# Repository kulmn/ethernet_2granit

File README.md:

# Устройство прозрачной передачи данных с КП «Гранит» («Гранит М») через Ethernet сеть.

Непосредственно опрашивает КП, ответ упаковывает в UDP пакет и отправляет на указанный IP и порт. Приёмная сторона передаёт данные в последовательный порт.

- веб интерфейс настройки параметров (IP адрес, шлюз, скорость портов, адреса КП) 
- 1 Ethernet и 2 последовательных порта
- кнопка сброса к заводским настройкам
- Сторожевой таймер

Hardware:
- Schematic diagram (Autodesk EAGLE and PDF) in /schematic/ dir
- MCU: STM32F030K6
- ENC28J60 china module

Firmvare:
- GCC Eclipse project, FreeRTOS, LibopenCM3

##### !!! Использовать только в защищённых сетях !!!

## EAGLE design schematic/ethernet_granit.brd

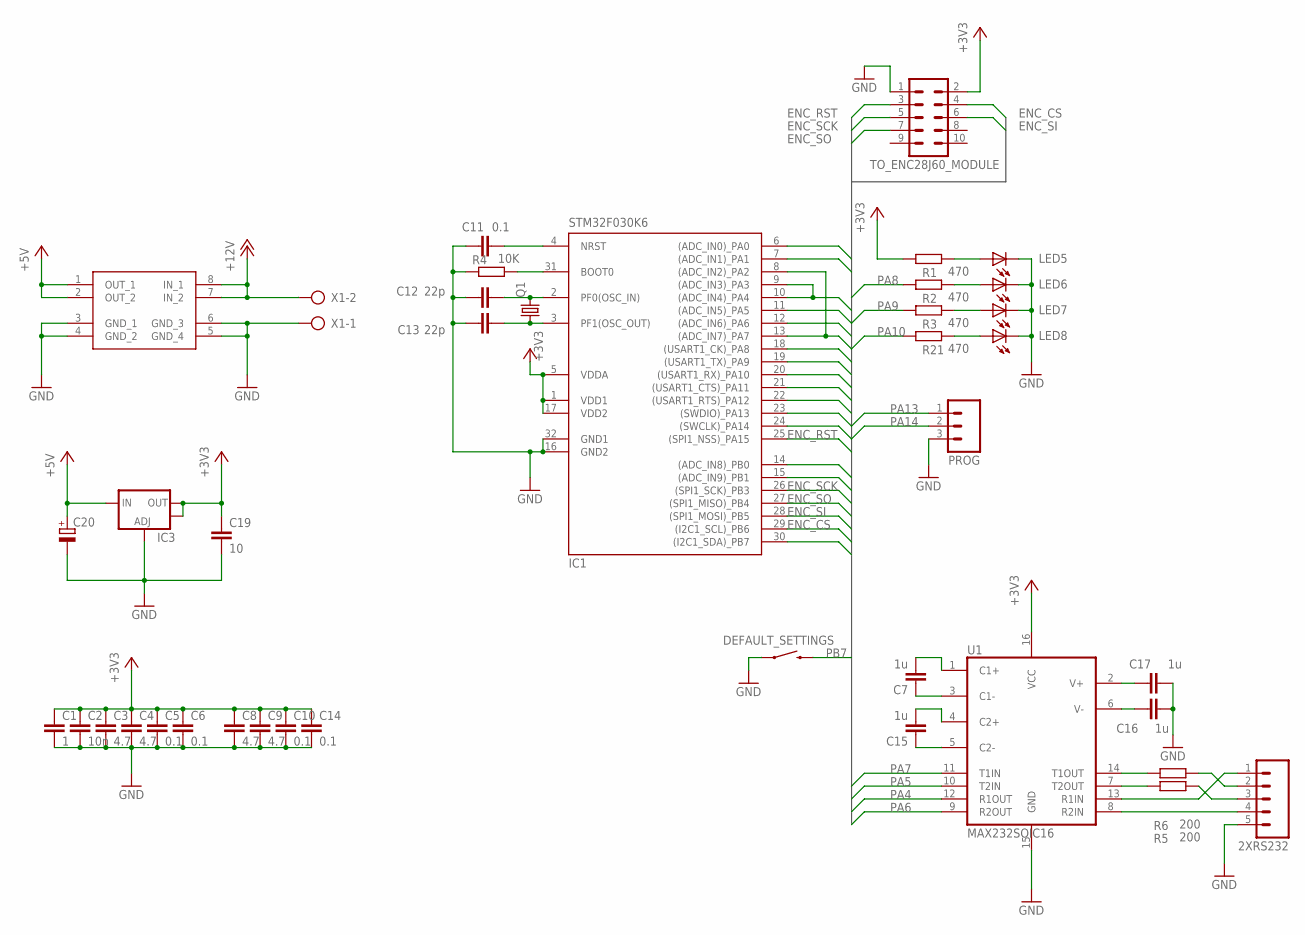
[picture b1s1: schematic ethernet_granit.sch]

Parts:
2XRS232: M05; 05P
C1: 1; C0805
C2: 10n; C0805
C3, C4, C8, C9: 4.7; C0805
C5, C6, C10, C11, C14: 0.1; C0805
C7, C15, C16, C17: 1u; C0805
C12, C13: 22p; C0805
C19: 10; C0805
C20: CPOL-EUSMCC; SMC_C
DEFAULT_SETTINGS: SWITCH-MOMENTARY-2SIDE_EZ; TACTILE-PTH-SIDEEZ
IC1: STM32F030K6; TQFP32-08
IC3: V_REG_LM1117SOT223; SOT223
LED5, LED6, LED7, LED8: TLLG4400; LED3MM
PROG: M03; 03P
Q1: CRYSTALHC49S; HC49/S
R1, R2, R3, R21: 470; R0805
R4: 10K; R0805
R5, R6: 200; R0805
TO_ENC28J60_MODULE: ML10L
U1: MAX232SOIC16; SO016
U$1: MP1584_MODUL
X1: AK300/2

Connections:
+3V3: C1.1, C2.1, C3.1, C4.1, C5.1, C6.1, C8.1, C9.1, C10.1, C14.1, C19.1, IC1.1 (VDD1), IC1.5 (VDDA), IC1.17 (VDD2), IC3.2 (OUT), IC3.4 (OUT), R1.1, TO_ENC28J60_MODULE.2, U1.16 (VCC)
+5V: C20.+, IC3.3 (IN), U$1.1 (OUT_1), U$1.2 (OUT_2)
+12V: U$1.7 (IN_2), U$1.8 (IN_1), X1.2
ENC_CS: IC1.29 ((I2C1_SCL)_PB6), TO_ENC28J60_MODULE.4
ENC_RST: IC1.25 ((SPI1_NSS)_PA15), TO_ENC28J60_MODULE.3
ENC_SCK: IC1.26 ((SPI1_SCK)_PB3), TO_ENC28J60_MODULE.5
ENC_SI: IC1.28 ((SPI1_MOSI)_PB5), TO_ENC28J60_MODULE.6
ENC_SO: IC1.27 ((SPI1_MISO)_PB4), TO_ENC28J60_MODULE.7
GND: 2XRS232.5, C1.2, C2.2, C3.2, C4.2, C5.2, C6.2, C8.2, C9.2, C10.2, C11.1, C12.1, C13.1, C14.2, C16.1, C17.1, C19.2, C20.-, DEFAULT_SETTINGS.1, IC1.16 (GND2), IC1.32 (GND1), IC3.1 (ADJ), LED5.K (C), LED6.K (C), LED7.K (C), LED8.K (C), PROG.3, R4.1, TO_ENC28J60_MODULE.1, U1.15 (GND), U$1.3 (GND_1), U$1.4 (GND_2), U$1.5 (GND_4), U$1.6 (GND_3), X1.1
unnamed: C7.1, U1.3 (C1-)
unnamed: C7.2, U1.1 (C1+)
unnamed: C12.2, IC1.2 (PF0(OSC_IN)), Q1.2
unnamed: C13.2, IC1.3 (PF1(OSC_OUT)), Q1.1
unnamed: C15.1, U1.5 (C2-)
unnamed: C15.2, U1.4 (C2+)
unnamed: IC1.31 (BOOT0), R4.2
unnamed: C17.2, U1.2 (V+)
unnamed: C16.2, U1.6 (V-)
unnamed: LED5.A, R1.2
unnamed: R6.1, U1.14 (T1OUT)
unnamed: 2XRS232.3, R5.2
unnamed: R5.1, U1.7 (T2OUT)
unnamed: 2XRS232.4, U1.8 (R2IN)
unnamed: LED6.A, R2.2
unnamed: LED7.A, R3.2
unnamed: LED8.A, R21.2
unnamed: 2XRS232.2, R6.2
unnamed: 2XRS232.1, U1.13 (R1IN)
unnamed: C11.2, IC1.4 (NRST)
PA0: IC1.6 ((ADC_IN0)_PA0)
PA1: IC1.7 ((ADC_IN1)_PA1)
PA4: IC1.9 ((ADC_IN3)_PA3), IC1.10 ((ADC_IN4)_PA4), U1.12 (R1OUT)
PA5: IC1.11 ((ADC_IN5)_PA5), U1.10 (T2IN)
PA6: IC1.12 ((ADC_IN6)_PA6), U1.9 (R2OUT)
PA7: IC1.8 ((ADC_IN2)_PA2), IC1.13 ((ADC_IN7)_PA7), U1.11 (T1IN)
PA8: IC1.18 ((USART1_CK)_PA8), R2.1
PA9: IC1.19 ((USART1_TX)_PA9), R3.1
PA10: IC1.20 ((USART1_RX)_PA10), R21.1
PA11: IC1.21 ((USART1_CTS)_PA11)
PA12: IC1.22 ((USART1_RTS)_PA12)
PA13: IC1.23 ((SWDIO)_PA13), PROG.1
PA14: IC1.24 ((SWCLK)_PA14), PROG.2
PB0: IC1.14 ((ADC_IN8)_PB0)
PB1: IC1.15 ((ADC_IN9)_PB1)
PB7: DEFAULT_SETTINGS.2, IC1.30 ((I2C1_SDA)_PB7)

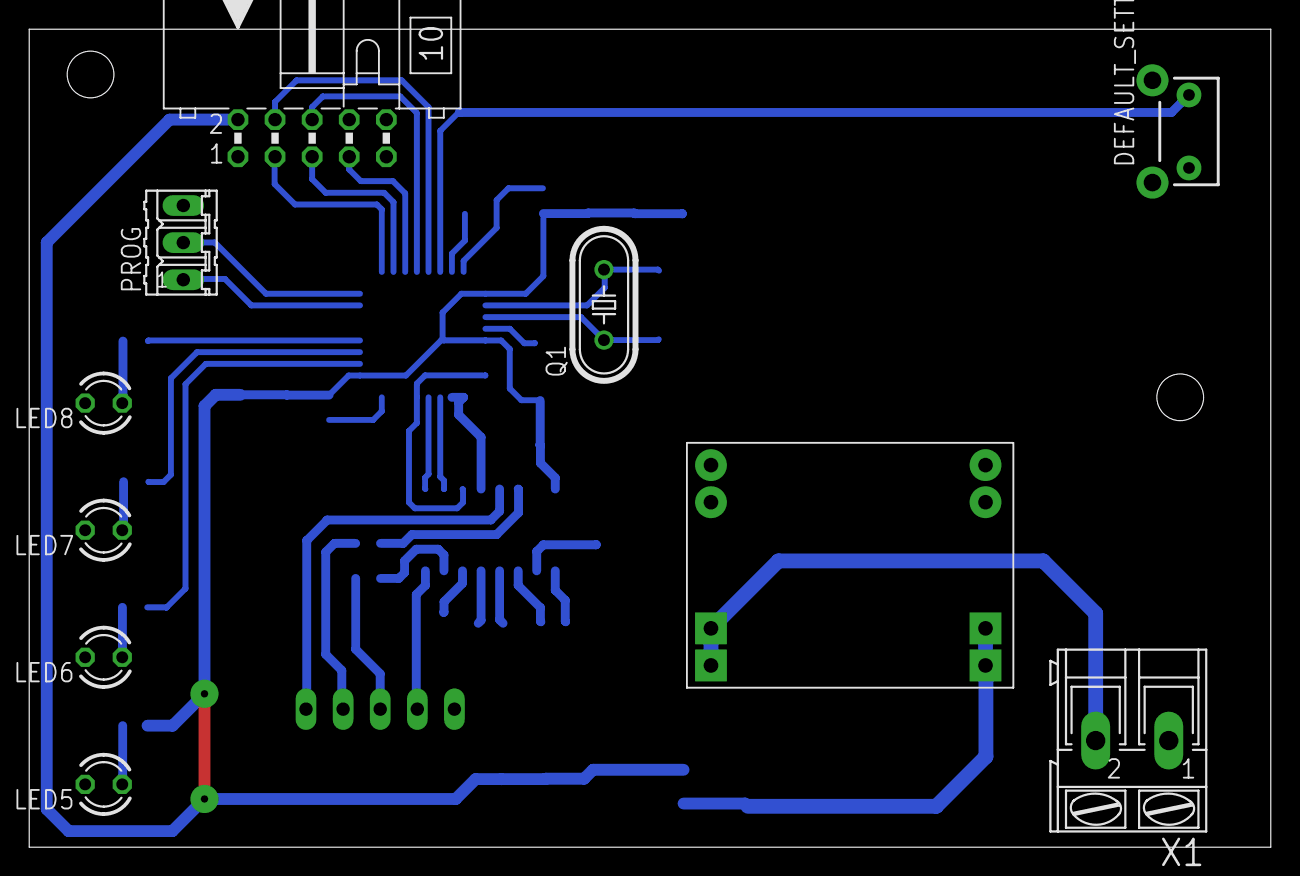
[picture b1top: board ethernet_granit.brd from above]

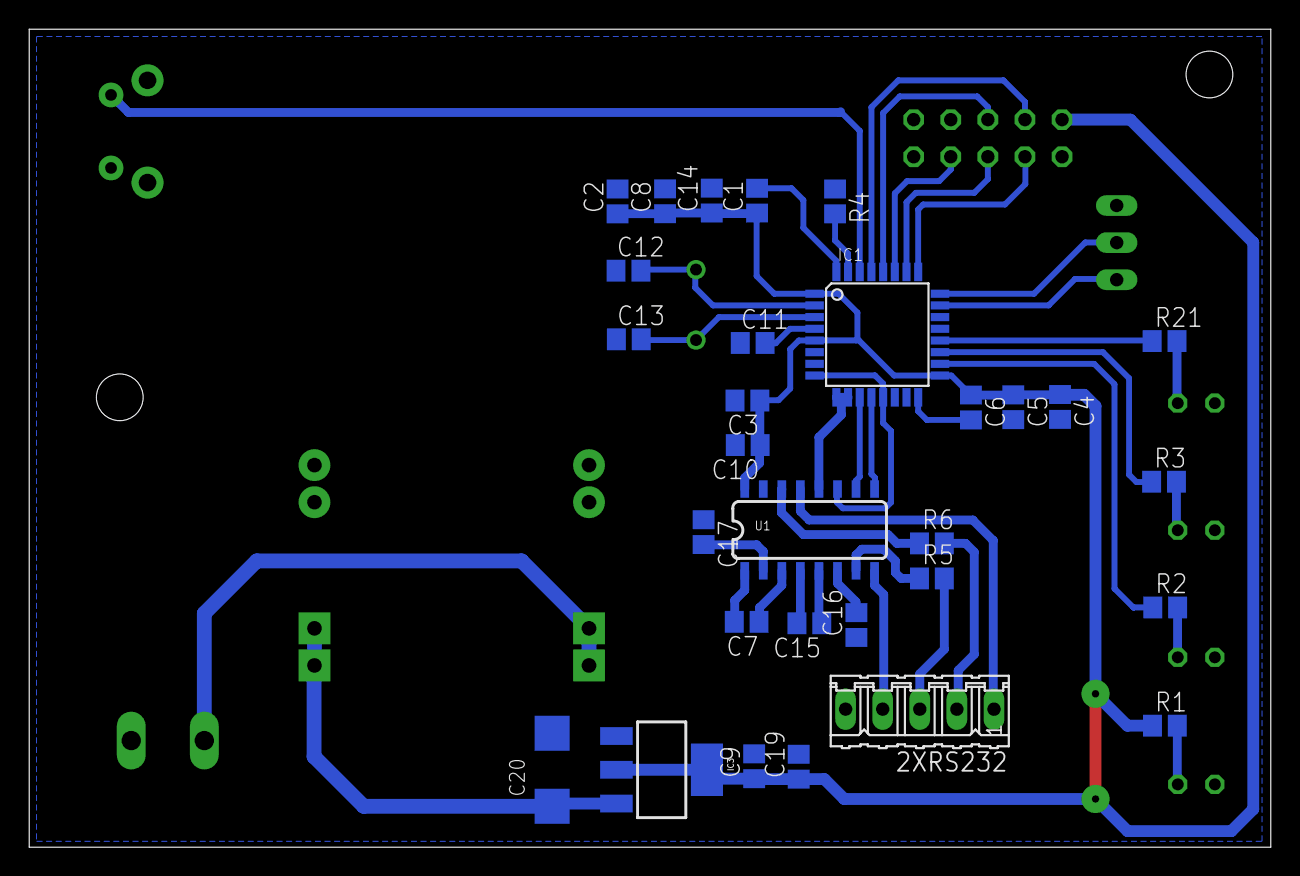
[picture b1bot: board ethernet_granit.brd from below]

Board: 2 copper layers, 85.0 x 56.0 mm, 40 parts (30 on the bottom side), 39 nets.

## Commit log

2021-03-02 init
2021-03-02 add schematic
2021-03-02 Create LICENSE

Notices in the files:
parts and their libraries:
SparkFun-DigitalIC: Licensing: Creative Commons ShareAlike 4.0 International - https://creativecommons.org/licenses/by-sa/4.0
SparkFun: Licensing: CC v3.0 Share-Alike You are welcome to use this library for commercial purposes.
